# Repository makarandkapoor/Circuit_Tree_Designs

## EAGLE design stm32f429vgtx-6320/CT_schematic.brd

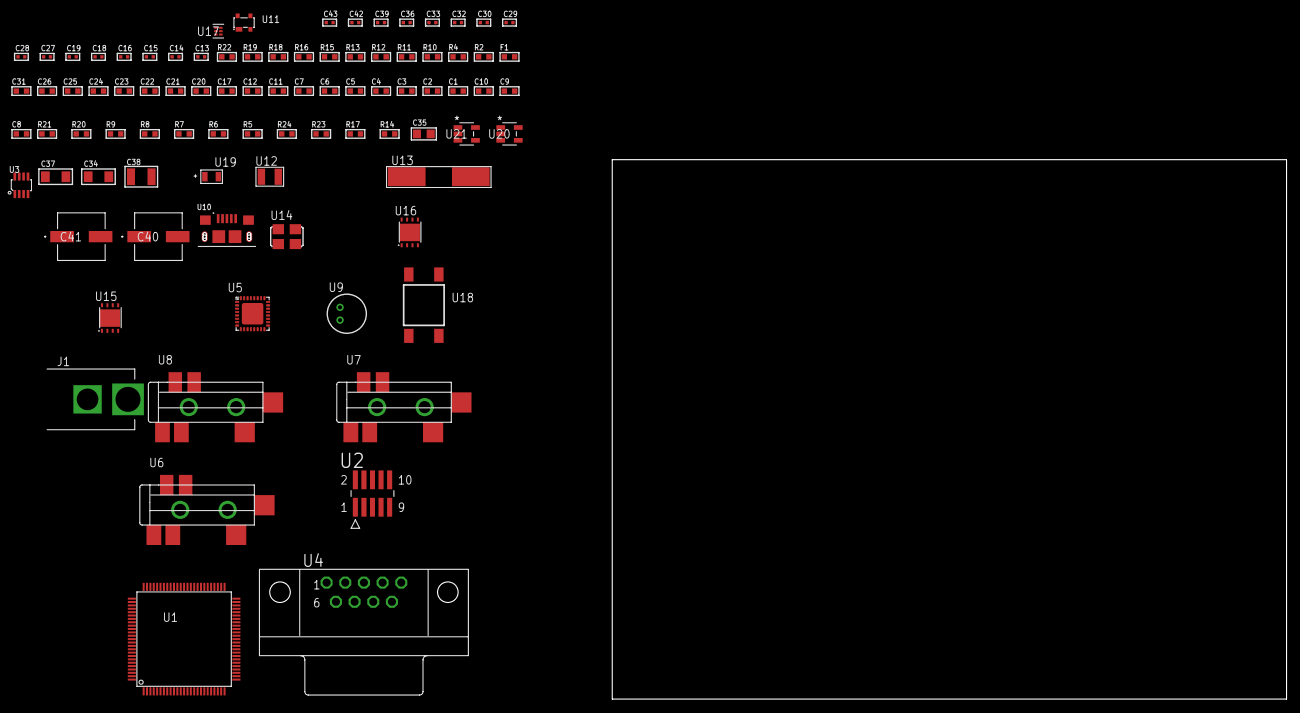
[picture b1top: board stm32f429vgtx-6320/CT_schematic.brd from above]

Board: 2 copper layers, 88 parts (0 on the bottom side), 56 nets, no tracks yet.

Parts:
C1, C12, C17, C20, C21, C22, C23, C24, C25, C26, C31: 1e-06; C0603
C2, C3, C4, C5, C6, C7: 1e-07; C0603
C8: 4.7e-06; C0603
C9, C10: 2.2e-09; C0603
C11: 1e-08; C0603
C13, C14, C15, C16: 1e-11; C0402
C18, C19, C27, C28, C29, C30, C39: 1e-07; C0402
C32, C33, C36, C42, C43: 1e-08; C0402
C34, C37: 1e-05; C1206
C35: 1e-05; C0805
C38: 1e-05; C1210
C40, C41: 0.0001; EXV-9H
F1: 240.0; L0603
J1: PJ-037B; PJ-037B_PACKAGE
R2, R16, R19: 1000.0; R0603
R4: 4700.0; R0603
R5, R6, R7, R8, R9, R20, R21: 10000.0; R0603
R10: 5.0; R0603
R11: 120.0; R0603
R12, R13: 1270.0; R0603
R14, R17: 100000.0; R0603
R15: 200.0; R0603
R18: 2231.0; R0603
R22: 9100.0; R0603
R23: 680000.0; R0603
R24: 120000.0; R0603
U1: STM32F429VGT6; LQFP100
U2: FTSH-105-01-L-DV-K; SAMTEC_FTSH-105-01-L-DV-K
U3: MAX3051EKA+T; SOT-23-8
U4: 182-009-113R531; 182-009-MALE
U5: SGTL5000XNAA3; QFN-32
U6, U7, U8: SJ-43515TS-SMT-TR
U9: WM-64PCT; WM-64PC
U10: 10118193-0001LF; FCI_10118193-0001LF
U11: prtr5v0u2ax; SOT143B
U12: ABS07-32.768KHZ-7-T
U13: ABLS-25.000MHZ-B2F-T
U14: ASFL-24.57MHZ-NCS; ASFL1
U15, U16: LP3878SDX-ADJ/NOPB; WSON-8
U17: TPS3895ADRYR; SON-6
U18: 4-1437565-2; SW_4-1437565-2
U19: Q65110A2395; LGM67K-G1J2-24-Z
U20, U21: nc7sz125m5x; NC7SZ125M5X

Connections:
CLK_CRYSTAL_U1_8: C13.1, U1.8, U12.1
CLK_CRYSTAL_U1_9: C14.1, U1.9, U12.2
CLK_CRYSTAL_U1_12: C15.1, U1.12, U13.1
CLK_CRYSTAL_U1_13: C16.1, U1.13, U13.2
CLK_U5_21: U5.21, U14.3
GND: C1.2, C2.2, C3.2, C4.2, C5.2, C6.2, C7.2, C8.2, C9.2, C10.2, C11.2, C12.2, C13.2, C14.2, C15.2, C16.2, C17.2, C18.2, C19.2, C27.2, C28.2, C29.2, C30.2, C31.2, C32.2, C33.2, C34.2, C35.2, C36.2, C37.2, C38.2, C39.2, C40.2, C41.2, C42.2, C43.2, J1.2, R2.2, R6.2, R10.2, R13.2, R16.2, R19.2, R22.2, R24.2, U1.10, U1.20, U1.27, U1.70, U1.74, U1.99, U2.3, U2.5, U3.2, U3.8, U4.5, U5.1, U5.3, U5.7, U5.EXP, U7.1, U8.1, U9.2, U10.5, U10.6, U10.7, U10.8, U10.9, U11.1, U14.2, U15.3, U15.PAD, U16.3, U16.PAD, U17.2, U19.C, U20.2, U20.3, U21.1, U21.3
NET_U1_14: R4.1, U1.14, U21.4
NET_U1_22: C11.1, C12.1, F1.1, U1.21, U1.22
NET_U1_37: R6.1, U1.37
NET_U1_49: C9.1, U1.49
NET_U1_73: C10.1, U1.73
NET_U1_94: R5.1, U1.94
NET_U1_98: U18.3, U18.4
NET_U2_9: R10.1, U2.9
NET_U3_6: R11.2, U3.6
NET_U4_2: R11.2, U3.6, U4.2
NET_U4_3: R11.1, U3.7, U4.3
NET_U5_10: C30.1, U5.10
NET_U5_29: R12.1, U5.29
NET_U5_31: R13.1, U5.31
NET_U6_1: U5.4, U6.1
NET_U6_2: U5.2, U6.2
NET_U6_5: U5.6, U6.5
NET_U7_2: C21.1, U7.2
NET_U7_5: C20.1, U7.5
NET_U8_2: C23.1, C24.1, U8.2
NET_U8_5: C22.1, U8.5
NET_U8_13: C23.2, C24.2
NET_U9_1: C25.1, C26.1, C31.1, U5.16, U9.1
NET_U9_15: C25.2, C26.2
NET_U15_1: C33.1, U15.1
NET_U15_6: R15.2, R16.1, U15.6
NET_U15_8: R14.1, U15.8
NET_U16_1: C36.1, U16.1
NET_U16_6: R18.2, R19.1, U16.6
NET_U16_8: R17.1, U16.8
NET_U17_1: R21.1, R22.1, U17.1
NET_U17_3: R23.2, R24.1, U17.3
NET_U17_4: R20.1, U17.4, U20.4, U21.2
NET_U18_1: R2.1, U18.1, U18.2
PROC_CAN1_RX: U1.81, U3.4
PROC_CAN1_TX: U1.82, U3.1
PROC_I2S2_CK: U1.47, U5.24
PROC_I2S2_EXT_SD: U1.17, U5.25
PROC_I2S2_SD: U1.18, U5.26
PROC_I2S2_WS: U1.51, U5.23
PROC_SYS_JTCK_SWCLK: R8.1, U1.76, U2.4
PROC_SYS_JTDO_SWO: U1.89, U2.6
PROC_SYS_JTMS_SWDIO: R9.1, U1.72, U2.2
PROC_USB_OTG_FS_DM: U1.70, U10.2, U11.3
PROC_USB_OTG_FS_DP: U1.71, U10.3, U11.2
PROC_USB_OTG_FS_VBUS: C17.1, U1.68, U10.1, U11.4
RST_OUT_U2_JTAG_RST_B: R7.1, U2.10, U20.1
VCC_S1_5V6: C34.1, C37.1, C40.1, C41.1, J1.1, R14.2, R17.2, U15.4, U16.4
VCC_TIER1_1V2: C27.1, C35.1, R15.1, U5.30, U15.5
VCC_TIER1_3V3: C1.1, C2.1, C3.1, C4.1, C5.1, C6.1, C7.1, C8.1, C18.1, C19.1, C28.1, C29.1, C32.1, C38.1, C39.1, C42.1, C43.1, F1.2, R4.2, R5.2, R7.2, R8.2, R9.2, R12.2, R18.1, R20.2, R21.2, R23.1, U1.6, U1.11, U1.19, U1.28, U1.50, U1.75, U1.100, U2.1, U3.3, U5.5, U5.20, U14.4, U16.5, U17.6, U20.5, U21.5

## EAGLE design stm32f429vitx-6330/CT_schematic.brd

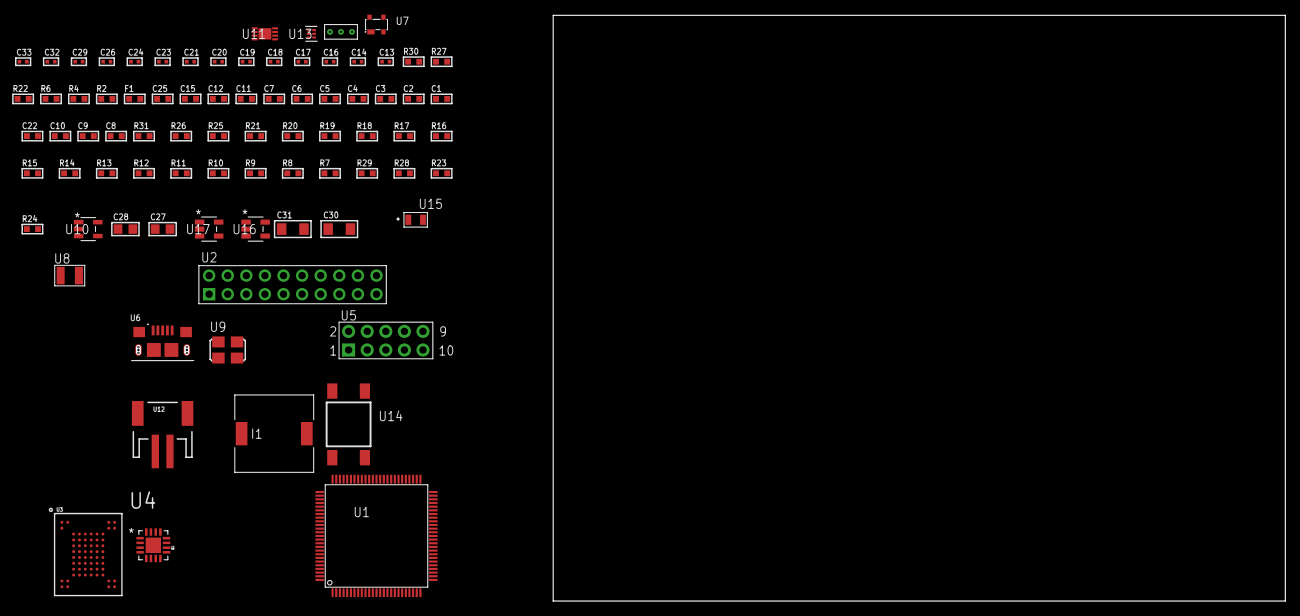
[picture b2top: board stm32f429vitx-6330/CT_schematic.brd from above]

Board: 2 copper layers, 81 parts (0 on the bottom side), 56 nets, no tracks yet.

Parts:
C1, C12, C15, C25: 1e-06; C0603
C2, C3, C4, C5, C6, C7: 1e-07; C0603
C8: 4.7e-06; C0603
C9, C10: 2.2e-09; C0603
C11: 1e-08; C0603
C13, C14: 1e-11; C0402
C16, C17, C18, C19, C20, C21, C23, C24, C29: 1e-07; C0402
C22: 2.2e-06; C0603
C26, C32, C33: 1e-08; C0402
C27, C28: 1e-05; C0805
C30, C31: 1e-05; C1206
F1: 240.0; L0603
I1: 2.5e-06; DR1040
R2: 1000.0; R0603
R4: 4700.0; R0603
R6: 2200.0; R0603
R7, R8, R9, R10, R11, R12, R13, R14, R15, R16, R17, R18, R19, R20, R21, R25, R26, R31: 10000.0; R0603
R22: 47.0; R0603
R23: 220000.0; R0603
R24: 1000000.0; R0603
R27: 9100.0; R0603
R28: 680000.0; R0603
R29: 120000.0; R0603
R30: 2000.0; R0603
U1: STM32F429VIT6; LQFP100
U2: TST-110-05-T-D-RA
U3: mt29f4g08abadah4; VFBGA-63
U4: TSC2013QRSARQ1; QFN65P400X400X100-17N
U5: HTSS-105-01-G-D
U6: 10118193-0001LF; FCI_10118193-0001LF
U7: prtr5v0u2ax; SOT143B
U8: ABS07-32.768KHZ-7-T
U9: ASFL1-25MHZ-NCS; ASFL1
U10: ltc3406es5; TSOT-23-5
U11: MCP73831T-2ACI/MC; DFN8_2X3MC
U12: S2B-PH-SM4-TB(LF)(SN); JST-2-SMD
U13: TPS3895ADRYR; SON-6
U14: 4-1437565-2; SW_4-1437565-2
U15: Q65110A2395; LGM67K-G1J2-24-Z
U16, U17: nc7sz125m5x; NC7SZ125M5X
U18: Dummy; DUMMY_PACKAGE_174

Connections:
CLK_CRYSTAL_U1_8: C13.1, U1.8, U8.1
CLK_CRYSTAL_U1_9: C14.1, U1.9, U8.2
CLK_U1_12: U1.12, U9.3
GND: C1.2, C2.2, C3.2, C4.2, C5.2, C6.2, C7.2, C8.2, C9.2, C10.2, C11.2, C12.2, C13.2, C14.2, C15.2, C16.2, C17.2, C18.2, C19.2, C20.2, C21.2, C22.2, C26.2, C27.2, C28.1, C28.2, C29.2, C30.2, C31.2, C32.2, C33.2, R2.2, R8.2, R14.2, R23.2, R27.2, R29.2, R30.2, U1.10, U1.20, U1.27, U1.70, U1.74, U1.99, U2.4, U2.6, U2.8, U2.10, U2.12, U2.14, U2.16, U2.18, U2.20, U3.C5, U3.F7, U3.K3, U3.K8, U4.17, U5.9, U6.5, U6.6, U6.7, U6.8, U6.9, U7.1, U9.2, U10.2, U11.6, U11.9, U12.2, U13.2, U15.C, U16.2, U16.3, U17.1, U17.3, U18.1
INPUT_USBPOWER_5V: C15.1, C30.1, R31.2, U1.68, U6.1, U7.4, U11.1, U11.2
NET_U1_14: R4.1, U1.14, U17.4
NET_U1_22: C11.1, C12.1, F1.1, U1.21, U1.22
NET_U1_37: R8.1, U1.37
NET_U1_49: C9.1, U1.49
NET_U1_73: C10.1, U1.73
NET_U1_93: R6.1, U1.93, U4.1
NET_U1_94: R7.1, U1.94
NET_U1_98: U14.3, U14.4
NET_U2_19: R14.1, U2.19
NET_U3_C3: R19.1, U3.C3
NET_U3_C8: R15.1, U3.C8
NET_U4_4: R21.1, U4.4
NET_U4_5: R20.1, U4.5
NET_U4_9: C23.2, C24.2, C25.2, R22.2, U4.9
NET_U4_15: R22.1, U4.8, U4.15
NET_U5_3: U4.12, U5.3
NET_U5_4: U4.14, U5.4
NET_U5_5: U4.11, U5.5
NET_U5_6: U4.13, U5.6
NET_U10_3: I1.1, U10.3
NET_U10_5: R23.1, R24.1, U10.5
NET_U10_ATNET_3: I1.2, R24.2
NET_U11_5: R31.1, U11.5
NET_U11_8: R30.1, U11.8
NET_U13_1: R26.1, R27.1, U13.1
NET_U13_3: R28.2, R29.1, U13.3
NET_U13_4: R25.1, U13.4, U16.4, U17.2
NET_U14_1: R2.1, U14.1, U14.2
PROC_FMC_D0: U1.61, U3.H4
PROC_FMC_D1: U1.62, U3.J4
PROC_FMC_D2: U1.81, U3.K4
PROC_FMC_D3: U1.82, U3.K5
PROC_FMC_D4: U1.38, U3.K6
PROC_FMC_D5: U1.39, U3.J7
PROC_FMC_D6: U1.40, U3.K7
PROC_FMC_D7: U1.41, U3.J8
PROC_FMC_NCE2: R16.1, U1.88, U3.C6
PROC_FMC_NOE: R18.1, U1.85, U3.D4
PROC_FMC_NWE: R17.1, U1.86, U3.C7
PROC_SYS_JTCK_SWCLK: R12.1, U1.76, U2.9
PROC_SYS_JTDI: R10.1, U1.77, U2.5
PROC_SYS_JTDO_SWO: U1.89, U2.13
PROC_SYS_JTMS_SWDIO: R11.1, U1.72, U2.7
PROC_SYS_JTRST: R9.1, U1.90, U2.3
PROC_TIM1_CH2: U1.42, U18.2
PROC_TIM1_CH4: U1.45, U18.3
PROC_USB_OTG_FS_DM: U1.70, U6.2, U7.3
PROC_USB_OTG_FS_DP: U1.71, U6.3, U7.2
RST_OUT_U2_SRESET_B: R13.1, U2.15, U16.1
VCC_S1_3V7: C27.1, C31.1, U10.4, U11.3, U11.4, U12.1
VCC_TIER1_3V3: C1.1, C2.1, C3.1, C4.1, C5.1, C6.1, C7.1, C8.1, C16.1, C17.1, C18.1, C19.1, C20.1, C21.1, C22.1, C23.1, C24.1, C25.1, C26.1, C28.2, C29.1, C32.1, C33.1, F1.2, I1.2, R4.2, R6.2, R7.2, R9.2, R10.2, R11.2, R12.2, R13.2, R15.2, R16.2, R17.2, R18.2, R19.2, R20.2, R21.2, R24.2, R25.2, R26.2, R28.1, U1.6, U1.11, U1.19, U1.28, U1.50, U1.75, U1.100, U2.1, U2.2, U3.D3, U3.G4, U3.H8, U3.J6, U4.7, U4.10, U9.4, U13.6, U16.5, U17.5

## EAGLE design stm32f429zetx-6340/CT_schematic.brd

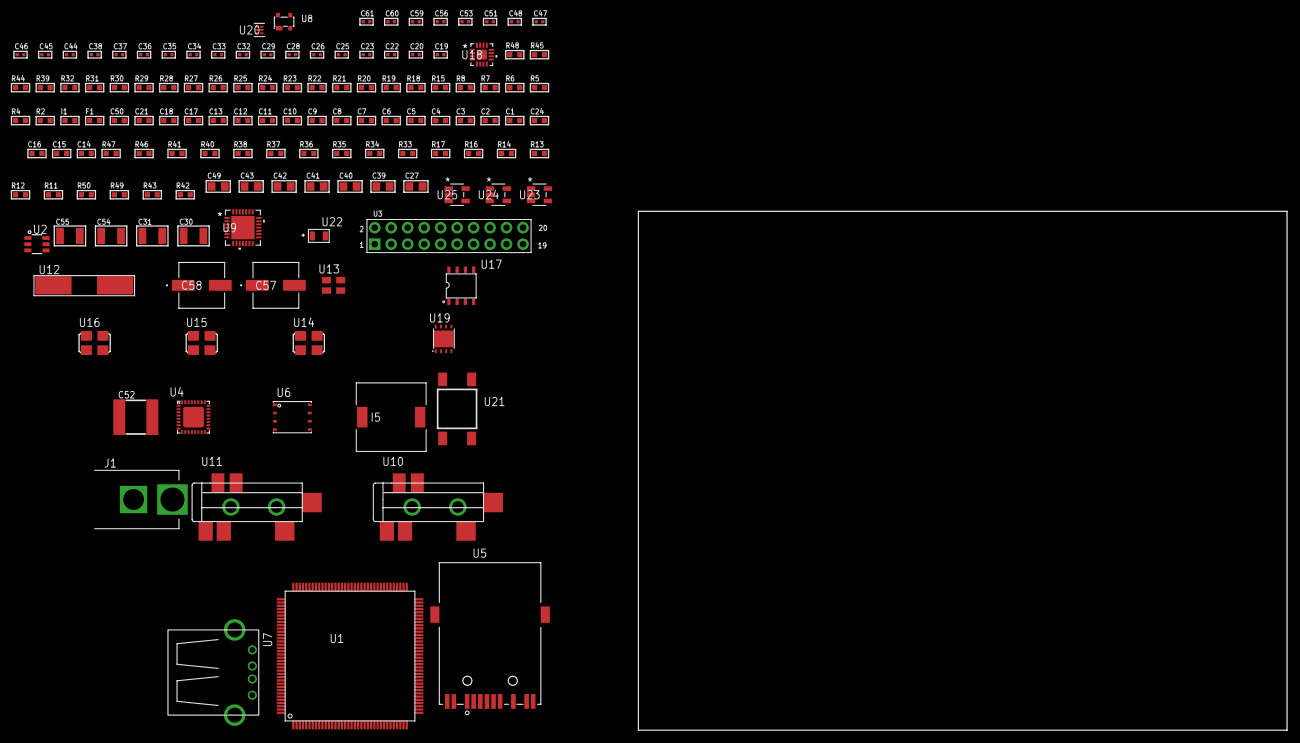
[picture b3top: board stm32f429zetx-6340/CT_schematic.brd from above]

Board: 2 copper layers, 100.0 x 80.0 mm, 136 parts (0 on the bottom side), 91 nets, no tracks yet.

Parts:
C1, C18, C21, C50: 1e-06; C0603
C2, C3, C4, C5, C6, C7, C8, C9, C10, C11, C12, C13: 1e-07; C0603
C14: 4.7e-06; C0603
C15, C16: 2.2e-09; C0603
C17: 1e-08; C0603
C19, C20: 1e-11; C0402
C22, C23, C25, C26, C28, C34, C35, C36, C37, C38, C51, C56: 1e-07; C0402
C24: 2.2e-06; C0603
C27, C39, C40, C41, C42, C43, C49: 1e-05; C0805
C29, C44, C45, C46, C47, C48, C53, C59, C60, C61: 1e-08; C0402
C30, C31: 2.2e-05; C1210
C32, C33: 1e-09; C0402
C52: 6.8e-05; 2220
C54, C55: 1e-05; C1210
C57, C58: 0.0001; EXV-9H
F1: 240.0; L0603
I1: 97.0; R0603
I5: 7e-06; DR1040
J1: PJ-037B; PJ-037B_PACKAGE
R2, R27, R29, R30, R45: 1000.0; R0603
R4, R5, R6, R23, R24, R25, R26, R28, R31, R32: 4700.0; R0603
R7, R8: 2200.0; R0603
R11, R36, R37, R38: 47000.0; R0603
R12, R13, R14, R16, R17, R33, R34, R35, R46, R47: 10000.0; R0603
R15: 1270.0; R0603
R18, R19: 0.1; R0603
R20: 200.0; R0603
R21: 220.0; R0603
R22: 6490.0; R0603
R39: 680.0; R0603
R40: 20000.0; R0603
R41: 91000.0; R0603
R42: 300000.0; R0603
R43: 100000.0; R0603
R44: 3900.0; R0603
R48: 9100.0; R0603
R49: 680000.0; R0603
R50: 120000.0; R0603
U1: STM32F429ZET6; LQFP144
U2: MAX4995AAUT+T; SOT-23-6
U3: arducam_ov2640; ARDUCAM
U4: KSZ8081RNBIA-TR; QFN-32
U5: 7498011122R
U6: 24AA256-I/MF; DFN8-S
U7: 61400416021; USB-A-H
U8: prtr5v0u2ax; SOT143B
U9: WM8731CLSEFL; QFN-28
U10, U11: SJ-43515TS-SMT-TR
U12: ABLS-25.000MHZ-B2F-T
U13: ASEK-32.768KHz-ECST; ASEK
U14: ASFL1-12.288MHZ-EC-T; ASFL1
U15: ASFL1-25MHZ-NCS; ASFL1
U16: ASFL1-50MHZ-NCS; ASFL1
U17: idt74fct38072; IDT74FCT38072
U18: LTC3601EUD#PBF; QFN-16_EP
U19: LP3878SDX-ADJ/NOPB; WSON-8
U20: TPS3895ADRYR; SON-6
U21: 4-1437565-2; SW_4-1437565-2
U22: Q65110A2395; LGM67K-G1J2-24-Z
U23, U24, U25: nc7sz125m5x; NC7SZ125M5X

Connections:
CLK_CRYSTAL_U1_23: C19.1, U1.23, U12.1
CLK_CRYSTAL_U1_24: C20.1, U1.24, U12.2
CLK_U1_8: U1.8, U13.3
CLK_U1_35: U1.35, U17.7
CLK_U3_8: U3.8, U15.3
CLK_U4_9: U4.9, U17.6
CLK_U9_1: U9.1, U14.3
CLK_U17_3: U16.3, U17.3
GND: C1.2, C2.2, C3.2, C4.2, C5.2, C6.2, C7.2, C8.2, C9.2, C10.2, C11.2, C12.2, C13.2, C14.2, C15.2, C16.2, C17.2, C18.2, C19.2, C20.2, C21.2, C22.2, C23.2, C24.2, C25.2, C26.2, C27.2, C28.2, C29.2, C33.2, C34.2, C35.2, C36.2, C37.2, C38.2, C39.2, C40.2, C41.2, C42.2, C43.2, C44.2, C45.2, C46.2, C47.2, C48.2, C49.2, C50.2, C52.1, C52.2, C53.2, C54.2, C55.2, C56.2, C57.2, C58.2, C59.2, C60.2, C61.2, J1.2, R2.2, R11.2, R14.2, R15.2, R17.2, R18.2, R19.2, R22.2, R24.2, R27.2, R29.2, R30.2, R33.2, R36.2, R37.2, R38.2, R40.2, R42.2, R45.2, R48.2, R50.2, U1.16, U1.31, U1.38, U1.51, U1.61, U1.83, U1.94, U1.107, U1.120, U1.130, U2.2, U3.2, U3.20, U4.1, U4.EXP, U5.1, U5.10, U6.4, U7.4, U7.5, U7.6, U8.1, U9.4, U9.15, U9.19, U9.25, U9.26, U9.29, U10.1, U11.1, U13.2, U14.2, U15.2, U16.2, U17.4, U17.5, U17.8, U18.1, U18.9, U18.17, U19.3, U19.PAD, U20.2, U22.C, U23.1, U23.3, U24.1, U24.3, U25.1, U25.3
NET_U1_25: R5.1, U1.25, U24.4
NET_U1_33: C17.1, C18.1, F1.1, U1.32, U1.33
NET_U1_48: R14.1, U1.48
NET_U1_71: C15.1, U1.71
NET_U1_102: R15.1, U1.102
NET_U1_106: C16.1, U1.106
NET_U1_136: R7.1, U1.136, U6.6
NET_U1_137: R8.1, U1.137, U6.5
NET_U1_138: R13.1, U1.138
NET_U1_142: U21.3, U21.4
NET_U1_143: R12.1, U1.143
NET_U2_3: R11.1, U2.3
NET_U3_19: R6.1, U3.19, U25.4
NET_U4_2: C24.1, C25.1, U4.2
NET_U4_3: C26.1, I1.1, U4.3
NET_U4_10: R22.1, U4.10
NET_U4_13: R25.1, U4.13
NET_U4_14: R26.1, U4.14
NET_U4_19: R24.1, U4.19
NET_U4_20: R30.1, U4.20
NET_U4_21: R23.1, U4.21
NET_U4_28: R28.1, U4.28
NET_U4_29: R29.1, U4.29
NET_U4_31: R31.1, U4.31
NET_U4_32: R4.1, U4.32, U23.4
NET_U5_1: U4.7, U5.1
NET_U5_2: C22.1, U5.2
NET_U5_3: U4.6, U5.3
NET_U5_4: U4.5, U5.4
NET_U5_5: C23.1, U5.5
NET_U5_6: U4.4, U5.6
NET_U5_8: R19.1, U5.8
NET_U5_9: R20.1, U5.9
NET_U5_12: R21.1, U5.12
NET_U5_13: R18.1, U5.13, U5.14
NET_U6_1: R33.1, U6.1
NET_U6_2: R34.1, U6.2
NET_U6_3: R35.1, U6.3
NET_U9_20: C38.1, C43.1, U9.20
NET_U10_2: C31.1, R37.1, U10.2
NET_U10_5: C30.1, R36.1, U10.5
NET_U11_5: C32.1, C33.1, R38.1, R39.1, U11.5
NET_U18_3: C51.2, I5.1, U18.3, U18.4
NET_U18_6: C51.1, U18.6
NET_U18_7: C50.1, U18.7, U18.12
NET_U18_10: R42.1, U18.10
NET_U18_11: R40.1, R41.1, U18.11
NET_U18_ATNET_3: I5.2, R41.2
NET_U19_1: C53.1, U19.1
NET_U19_6: R44.2, R45.1, U19.6
NET_U19_8: R43.1, U19.8
NET_U20_1: R47.1, R48.1, U20.1
NET_U20_3: R49.2, R50.1, U20.3
NET_U20_4: R46.1, U20.4, U23.2, U24.2, U25.2
NET_U21_1: R2.1, U21.1, U21.2
PROC_DCMI_D0: U1.96, U3.18
PROC_DCMI_D1: U1.97, U3.17
PROC_DCMI_D2: U1.98, U3.16
PROC_DCMI_D3: U1.99, U3.15
PROC_DCMI_D4: U1.3, U3.14
PROC_DCMI_D5: U1.117, U3.13
PROC_DCMI_D6: U1.4, U3.12
PROC_DCMI_D7: U1.5, U3.11
PROC_DCMI_D8: U1.111, U3.10
PROC_DCMI_D9: U1.113, U3.9
PROC_DCMI_HSYNC: U1.40, U3.6
PROC_DCMI_PIXCK: U1.42, U3.7
PROC_DCMI_VSYNC: U1.124, U3.5
PROC_ETH_RXD0: R32.1, U4.16
PROC_ETH_RXD1: R27.1, U4.15
PROC_GPIO_TO_U1_USB_FAULT: R16.1, U1.2, U2.6
PROC_GPIO_TO_U1_VBUS_EN: R17.1, U1.1, U2.4
PROC_I2S2_CK: U1.69, U9.7
PROC_I2S2_EXT_SD: U1.28, U9.10
PROC_I2S2_SD: U1.29, U9.8
PROC_I2S2_WS: U1.140, U9.9, U9.11
PROC_USB_OTG_FS_DM: U1.103, U7.2, U8.3
PROC_USB_OTG_FS_DP: U1.104, U7.3, U8.2
PROC_USB_OTG_FS_VBUS: U1.101, U2.1, U7.1, U8.4
VCC_S1_14V9: C49.1, C54.1, C57.1, C58.1, J1.1, R43.2, U18.15, U18.16, U19.4
VCC_TIER1_3V3: C1.1, C2.1, C3.1, C4.1, C5.1, C6.1, C7.1, C8.1, C9.1, C10.1, C11.1, C12.1, C13.1, C14.1, C21.1, C27.1, C28.1, C29.1, C34.1, C35.1, C36.1, C37.1, C39.1, C40.1, C41.1, C42.1, C44.1, C45.1, C46.1, C47.1, C48.1, C52.2, C56.1, C59.1, C60.1, C61.1, F1.2, I1.2, I5.2, R4.2, R5.2, R6.2, R7.2, R8.2, R12.2, R13.2, R16.2, R23.2, R25.2, R26.2, R28.2, R31.2, R32.2, R34.2, R35.2, R41.2, R46.2, R47.2, R49.1, U1.6, U1.17, U1.30, U1.39, U1.52, U1.62, U1.72, U1.84, U1.95, U1.108, U1.121, U1.131, U1.144, U3.1, U4.17, U6.7, U6.8, U9.3, U9.5, U9.12, U9.18, U13.4, U14.4, U15.4, U16.4, U17.1, U17.2, U18.8, U20.6, U23.5, U24.5, U25.5
VCC_TIER1_5V0: C55.1, R44.1, U2.5, U19.5

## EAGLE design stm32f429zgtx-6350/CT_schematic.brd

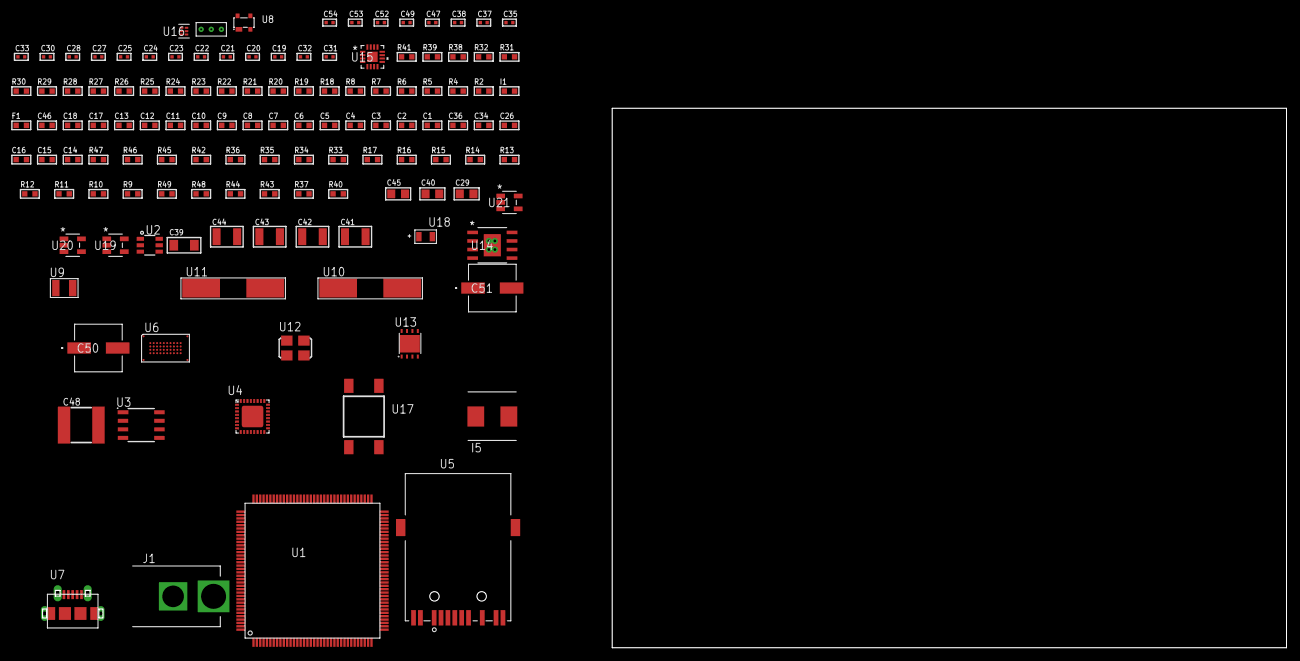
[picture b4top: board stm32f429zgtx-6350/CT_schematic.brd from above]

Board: 2 copper layers, 127 parts (0 on the bottom side), 110 nets, no tracks yet.

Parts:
C1, C18, C46: 1e-06; C0603
C2, C3, C4, C5, C6, C7, C8, C9, C10, C11, C12, C13: 1e-07; C0603
C14: 4.7e-06; C0603
C15, C16: 2.2e-09; C0603
C17: 1e-08; C0603
C19, C20, C21, C22: 1e-11; C0402
C23, C37, C38, C52, C53, C54: 1e-08; C0402
C24, C25, C27, C28, C30, C33, C35, C47, C49: 1e-07; C0402
C26, C34, C36: 2.2e-06; C0603
C29, C40, C45: 1e-05; C0805
C31, C32: 2.2e-11; C0402
C39: 1e-05; C1206
C41, C42, C43, C44: 1e-05; C1210
C48: 6.8e-05; 2220
C50, C51: 0.0001; EXV-9H
F1: 240.0; L0603
I1: 97.0; R0603
I5: 3.3e-06; WE-HCI_7030/7040/7050
J1: PJ-037B; PJ-037B_PACKAGE
R2, R25, R27, R29, R32, R39: 1000.0; R0603
R4, R5, R6, R23, R24, R26, R28, R30, R31: 4700.0; R0603
R7, R8, R41: 2200.0; R0603
R9: 47000.0; R0603
R10, R11, R12, R13, R14, R15, R16, R17, R33, R34, R35, R36, R45, R46: 10000.0; R0603
R18, R19: 0.1; R0603
R20: 200.0; R0603
R21: 220.0; R0603
R22: 6490.0; R0603
R37: 100000.0; R0603
R38: 806.0; R0603
R40: 4031.5447154472; R0603
R42: 20000.0; R0603
R43: 150000.0; R0603
R44, R48: 300000.0; R0603
R47: 82000.0; R0603
R49: 120000.0; R0603
U1: STM32F429ZGT6; LQFP144
U2: MAX4995AAUT+T; SOT-23-6
U3: AT25M02-SSHD-T; SOIC-8
U4: KSZ8081RNBIA-TR; QFN-32
U5: 7498011122R
U6: S29VS256RABBHW000
U7: 47590-0001; MICRO_USB_AB
U8: prtr5v0u2ax; SOT143B
U9: ABS07-32.768KHZ-7-T
U10, U11: ABLS-25.000MHZ-B2F-T
U12: ASFL1-50MHZ-NCS; ASFL1
U13: LP3878SDX-ADJ/NOPB; WSON-8
U14: MIC5234YME; SOIC-8_EP
U15: LTC3601EUD#PBF; QFN-16_EP
U16: TPS3895ADRYR; SON-6
U17: 4-1437565-2; SW_4-1437565-2
U18: Q65110A2395; LGM67K-G1J2-24-Z
U19, U20, U21: nc7sz125m5x; NC7SZ125M5X
U22: Dummy; DUMMY_PACKAGE_256

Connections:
CLK_CRYSTAL_U1_8: C19.1, U1.8, U9.1
CLK_CRYSTAL_U1_9: C20.1, U1.9, U9.2
CLK_CRYSTAL_U1_23: C21.1, U1.23, U10.1
CLK_CRYSTAL_U1_24: C22.1, U1.24, U10.2
CLK_CRYSTAL_U4_8: C31.1, U4.8, U11.2
CLK_CRYSTAL_U4_9: C32.1, U4.9, U11.1
CLK_U1_35: U1.35, U12.3
GND: C1.2, C2.2, C3.2, C4.2, C5.2, C6.2, C7.2, C8.2, C9.2, C10.2, C11.2, C12.2, C13.2, C14.2, C15.2, C16.2, C17.2, C18.2, C19.2, C20.2, C21.2, C22.2, C23.2, C24.2, C25.2, C26.2, C27.2, C28.2, C29.2, C30.2, C31.2, C32.2, C33.2, C34.2, C35.2, C36.2, C37.2, C38.2, C39.2, C40.2, C41.2, C42.2, C43.2, C44.2, C45.2, C46.2, C48.1, C48.2, C49.2, C50.2, C51.2, C52.2, C53.2, C54.2, J1.2, R2.2, R9.2, R12.2, R14.2, R18.2, R19.2, R22.2, R24.2, R25.2, R27.2, R29.2, R32.2, R39.2, R41.2, R42.2, R44.2, R47.2, R49.2, U1.16, U1.31, U1.38, U1.51, U1.61, U1.83, U1.94, U1.107, U1.120, U1.130, U2.2, U3.4, U4.1, U4.EXP, U5.1, U5.10, U6.C5, U6.D12, U6.E3, U6.F5, U7.5, U7.6, U7.7, U7.8, U7.9, U8.1, U12.2, U13.3, U13.PAD, U14.7, U14.EPAD, U15.1, U15.9, U15.17, U16.2, U18.C, U19.1, U19.3, U20.1, U20.3, U21.1, U21.3, U22.1
NET_U1_25: R6.1, U1.25, U21.4
NET_U1_27: R7.1, U1.27, U4.12
NET_U1_33: C17.1, C18.1, F1.1, U1.32, U1.33
NET_U1_36: R8.1, U1.36, U4.11
NET_U1_48: R12.1, U1.48
NET_U1_71: C15.1, U1.71
NET_U1_106: C16.1, U1.106
NET_U1_138: R11.1, U1.138
NET_U1_142: U17.3, U17.4
NET_U1_143: R10.1, U1.143
NET_U2_3: R9.1, U2.3
NET_U3_3: R15.1, U3.3
NET_U3_7: R17.1, U3.7
NET_U4_2: C26.1, C27.1, U4.2
NET_U4_3: C28.1, I1.1, U4.3
NET_U4_10: R22.1, U4.10
NET_U4_13: R25.1, U4.13
NET_U4_14: R26.1, U4.14
NET_U4_19: R24.1, U4.19
NET_U4_20: R30.1, U4.20
NET_U4_21: R23.1, U4.21
NET_U4_28: R28.1, U4.28
NET_U4_29: R29.1, U4.29
NET_U4_31: R31.1, U4.31
NET_U4_32: R4.1, U4.32, U19.4
NET_U5_1: U4.7, U5.1
NET_U5_2: C24.1, U5.2
NET_U5_3: U4.6, U5.3
NET_U5_4: U4.5, U5.4
NET_U5_5: C25.1, U5.5
NET_U5_6: U4.4, U5.6
NET_U5_8: R19.1, U5.8
NET_U5_9: R20.1, U5.9
NET_U5_12: R21.1, U5.12
NET_U5_13: R18.1, U5.13, U5.14
NET_U6_D8: R5.1, U6.D8, U20.4
NET_U13_1: C38.1, U13.1
NET_U13_6: R38.2, R39.1, U13.6
NET_U13_8: R37.1, U13.8
NET_U14_4: R40.2, R41.1, U14.4
NET_U15_3: C47.2, I5.1, U15.3, U15.4
NET_U15_6: C47.1, U15.6
NET_U15_7: C46.1, U15.7, U15.12
NET_U15_10: R44.1, U15.10
NET_U15_11: R42.1, R43.1, U15.11
NET_U15_ATNET_3: I5.2, R43.2
NET_U16_1: R46.1, R47.1, U16.1
NET_U16_3: R48.2, R49.1, U16.3
NET_U16_4: R45.1, U16.4, U19.2, U20.2, U21.2
NET_U17_1: R2.1, U17.1, U17.2
PROC_ADC1_IN3: U1.37, U22.2
PROC_ADC1_IN12: U1.28, U22.3
PROC_ETH_CRS_DV: U1.43, U4.18
PROC_ETH_RXD0: R32.1, U1.44, U4.16
PROC_ETH_RXD1: R27.1, U1.45, U4.15
PROC_ETH_TXD0: U1.73, U4.24
PROC_ETH_TXD1: U1.74, U4.25
PROC_ETH_TX_EN: U1.70, U4.23
PROC_FMC_A16: U1.80, U6.D4
PROC_FMC_A17: U1.81, U6.C11
PROC_FMC_A18: U1.82, U6.D10
PROC_FMC_A19: U1.2, U6.C10
PROC_FMC_A20: U1.3, U6.D5
PROC_FMC_A21: U1.4, U6.C4
PROC_FMC_A22: U1.5, U6.C12
PROC_FMC_A23: U1.1, U6.D7
PROC_FMC_CLK: U1.117, U6.C6
PROC_FMC_D0: U1.85, U6.F3
PROC_FMC_D1: U1.86, U6.F4
PROC_FMC_D2: U1.114, U6.E6
PROC_FMC_D3: U1.115, U6.E7
PROC_FMC_D4: U1.58, U6.F8
PROC_FMC_D5: U1.59, U6.F9
PROC_FMC_D6: U1.60, U6.E10
PROC_FMC_D7: U1.63, U6.E11
PROC_FMC_D8: U1.64, U6.E4
PROC_FMC_D9: U1.65, U6.E5
PROC_FMC_D10: U1.66, U6.F6
PROC_FMC_D11: U1.67, U6.F7
PROC_FMC_D12: U1.68, U6.E8
PROC_FMC_D13: U1.77, U6.E9
PROC_FMC_D14: U1.78, U6.F11
PROC_FMC_D15: U1.79, U6.F12
PROC_FMC_NE2: R34.1, U1.124, U6.D11
PROC_FMC_NL: U1.137, U6.D6
PROC_FMC_NOE: R36.1, U1.118, U6.E12
PROC_FMC_NWAIT: R33.1, U1.122, U6.C3
PROC_FMC_NWE: R35.1, U1.119, U6.C8
PROC_GPIO_TO_U1_USB_FAULT: R13.1, U1.10, U2.6
PROC_GPIO_TO_U1_VBUS_EN: R14.1, U1.7, U2.4
PROC_SPI1_MISO: U1.42, U3.2
PROC_SPI1_MOSI: U1.135, U3.5
PROC_SPI1_NSS: R16.1, U1.40, U3.1
PROC_SPI1_SCK: U1.41, U3.6
PROC_USB_OTG_FS_DM: U1.103, U7.2, U8.3
PROC_USB_OTG_FS_DP: U1.104, U7.3, U8.2
PROC_USB_OTG_FS_ID: U1.102, U7.4
PROC_USB_OTG_FS_VBUS: U1.101, U2.1, U7.1, U8.4
VCC_S1_5V9: C39.1, C41.1, C42.1, C45.1, C50.1, C51.1, J1.1, R37.2, U13.4, U14.5, U14.8, U15.15, U15.16
VCC_TIER1_1V8: C1.1, C2.1, C3.1, C4.1, C5.1, C6.1, C7.1, C8.1, C9.1, C10.1, C11.1, C12.1, C13.1, C14.1, C23.1, C29.1, C30.1, C33.1, C34.1, C35.1, C36.1, C40.1, C49.1, C52.1, C53.1, C54.1, F1.2, R4.2, R5.2, R6.2, R7.2, R8.2, R10.2, R11.2, R13.2, R15.2, R16.2, R17.2, R23.2, R26.2, R28.2, R30.2, R31.2, R33.2, R34.2, R35.2, R36.2, R38.1, R45.2, R46.2, R48.1, U1.6, U1.17, U1.30, U1.39, U1.52, U1.62, U1.72, U1.84, U1.95, U1.108, U1.121, U1.131, U1.144, U3.8, U4.17, U6.C7, U6.D3, U6.F10, U13.5, U16.6, U19.5, U20.5, U21.5
VCC_TIER1_3V3: C37.1, C43.1, C44.1, I1.2, R40.1, U12.4, U14.1
VCC_TIER1_5V0: C48.2, I5.2, R43.2, U2.5, U15.8

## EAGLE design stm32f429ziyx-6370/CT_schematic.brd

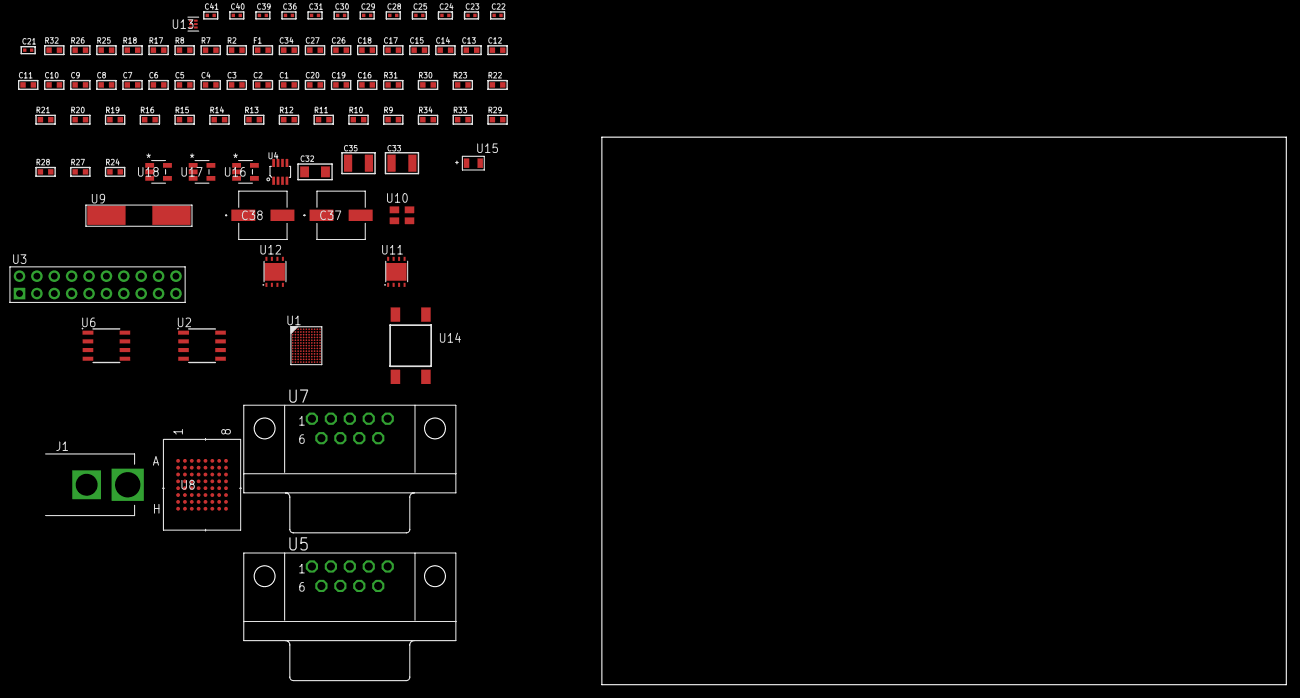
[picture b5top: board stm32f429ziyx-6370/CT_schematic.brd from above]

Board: 2 copper layers, 100.0 x 80.0 mm, 90 parts (0 on the bottom side), 92 nets, no tracks yet.

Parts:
C1, C18, C26, C27, C34: 1e-06; C0603
C2, C3, C4, C5, C6, C7, C8, C9, C10, C11, C12, C13, C14, C15: 1e-07; C0603
C16: 4.7e-06; C0603
C17: 1e-08; C0603
C19, C20: 2.2e-06; C0603
C21, C22: 1e-11; C0402
C23, C28, C29, C30, C31, C39, C40, C41: 1e-08; C0402
C24, C25, C36: 1e-07; C0402
C32: 1e-05; C1206
C33, C35: 1e-05; C1210
C37, C38: 0.0001; EXV-9H
F1: 240.0; L0603
J1: PJ-037B; PJ-037B_PACKAGE
R2, R26: 1000.0; R0603
R7, R8: 4700.0; R0603
R9, R10, R11, R12, R13, R14, R15, R16, R19, R20, R21, R22, R23, R30, R31: 10000.0; R0603
R17, R18: 120.0; R0603
R24, R27, R29: 100000.0; R0603
R25: 2231.0; R0603
R28: 300000.0; R0603
R32: 9100.0; R0603
R33: 680000.0; R0603
R34: 120000.0; R0603
U1: STM32F429ZIY6; WLCSP143
U2: AT25010B-SSHL-T; SOIC-8
U3: TST-110-05-T-D-RA
U4: MAX3051EKA+T; SOT-23-8
U5, U7: 182-009-113R531; 182-009-MALE
U6: MCP2562-E/SN; SOIC-8
U8: mt28ew256aba1HPC-0SIT; LBGA-64
U9: ABLS-25.000MHZ-B2F-T
U10: ASEK-32.768KHz-ECST; ASEK
U11: LP3878SDX-ADJ/NOPB; WSON-8
U12: LP2951ACSDX/NOPB; WSON-8
U13: TPS3895ADRYR; SON-6
U14: 4-1437565-2; SW_4-1437565-2
U15: Q65110A2395; LGM67K-G1J2-24-Z
U16, U17, U18: nc7sz125m5x; NC7SZ125M5X

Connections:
CLK_CRYSTAL_U1_H10: C21.1, U1.H10, U9.1
CLK_CRYSTAL_U1_J11: C22.1, U1.J11, U9.2
CLK_U1_D11: U1.D11, U10.3
GND: C1.2, C2.2, C3.2, C4.2, C5.2, C6.2, C7.2, C8.2, C9.2, C10.2, C11.2, C12.2, C13.2, C14.2, C15.2, C16.2, C17.2, C18.2, C19.2, C20.2, C21.2, C22.2, C23.2, C24.2, C25.2, C26.2, C27.2, C28.2, C29.2, C30.2, C31.2, C32.2, C33.2, C34.2, C35.2, C36.2, C37.2, C38.2, C39.2, C40.2, C41.2, J1.2, R2.2, R11.2, R12.2, R26.2, R29.2, R32.2, R34.2, U1.D2, U1.E7, U1.F5, U1.H2, U1.H3, U1.H7, U1.K10, U2.4, U3.4, U3.6, U3.8, U3.10, U3.12, U3.14, U3.16, U3.18, U3.20, U4.2, U4.8, U5.5, U6.2, U6.8, U7.5, U8.E8, U8.H2, U8.H7, U10.2, U11.3, U11.PAD, U12.3, U12.4, U12.PAD, U13.2, U15.C, U16.2, U16.3, U17.1, U17.3, U18.1, U18.3
NET_U1_A11: R9.1, U1.A11
NET_U1_C9: R10.1, U1.C9
NET_U1_D1: C20.1, U1.D1
NET_U1_H9: R8.1, U1.H9, U18.4
NET_U1_L7: R11.1, U1.L7
NET_U1_L10: C17.1, C18.1, F1.1, U1.L10, U1.L11
NET_U1_N2: C19.1, U1.N2
NET_U1_N10: U14.3, U14.4
NET_U1_N11: R12.1, U1.N11
NET_U2_3: R13.1, U2.3
NET_U2_7: R15.1, U2.7
NET_U4_6: R17.2, U4.6
NET_U5_2: R17.2, U4.6, U5.2
NET_U5_3: R17.1, U4.7, U5.3
NET_U6_6: R18.2, U6.6
NET_U7_2: R18.2, U6.6, U7.2
NET_U7_3: R18.1, U6.7, U7.3
NET_U8_B4: R22.1, U8.B4
NET_U8_B5: R7.1, U8.B5, U17.4
NET_U11_1: C31.1, U11.1
NET_U11_6: R25.2, R26.1, U11.6
NET_U11_8: R24.1, U11.8
NET_U12_5: R27.1, U12.5
NET_U12_7: R28.2, R29.1, U12.7
NET_U13_1: R31.1, R32.1, U13.1
NET_U13_3: R33.2, R34.1, U13.3
NET_U13_4: R30.1, U13.4, U16.4, U17.2, U18.2
NET_U14_1: R2.1, U14.1, U14.2
PROC_CAN1_RX: U1.A9, U4.4
PROC_CAN1_TX: U1.B9, U4.1
PROC_CAN2_RX: U1.M2, U6.4
PROC_CAN2_TX: U1.A8, U6.1
PROC_FMC_A0: U1.F11, U8.E2
PROC_FMC_A1: U1.E9, U8.D2
PROC_FMC_A2: U1.F10, U8.C2
PROC_FMC_A3: U1.G11, U8.A2
PROC_FMC_A4: U1.F9, U8.B2
PROC_FMC_A5: U1.F8, U8.D3
PROC_FMC_A6: U1.N7, U8.C3
PROC_FMC_A7: U1.K6, U8.A3
PROC_FMC_A8: U1.L6, U8.B6
PROC_FMC_A9: U1.M6, U8.A6
PROC_FMC_A10: U1.N6, U8.C6
PROC_FMC_A11: U1.K5, U8.D6
PROC_FMC_A12: U1.J1, U8.B7
PROC_FMC_A13: U1.G3, U8.A7
PROC_FMC_A14: U1.G5, U8.C7
PROC_FMC_A15: U1.G6, U8.D7
PROC_FMC_A16: U1.K2, U8.E7
PROC_FMC_A17: U1.H6, U8.B3
PROC_FMC_A18: U1.H5, U8.C4
PROC_FMC_A19: U1.C10, U8.D5
PROC_FMC_A20: U1.B11, U8.D4
PROC_FMC_A21: U1.D9, U8.C5
PROC_FMC_A22: U1.E8, U8.B8
PROC_FMC_A23: U1.D8, U8.C8
PROC_FMC_D0: U1.J2, U8.E3
PROC_FMC_D1: U1.K1, U8.H3
PROC_FMC_D2: U1.B3, U8.E4
PROC_FMC_D3: U1.C4, U8.H4
PROC_FMC_D4: U1.L5, U8.H5
PROC_FMC_D5: U1.M5, U8.E5
PROC_FMC_D6: U1.N5, U8.H6
PROC_FMC_D7: U1.J4, U8.E6
PROC_FMC_D8: U1.K4, U8.F3
PROC_FMC_D9: U1.L4, U8.G3
PROC_FMC_D10: U1.N4, U8.F4
PROC_FMC_D11: U1.M4, U8.G4
PROC_FMC_D12: U1.L3, U8.F5
PROC_FMC_D13: U1.L2, U8.G6
PROC_FMC_D14: U1.M1, U8.F6
PROC_FMC_D15: U1.H4, U8.G7
PROC_FMC_NBL0: R23.1, U1.B10, U8.F7
PROC_FMC_NE2: R19.1, U1.E5, U8.F2
PROC_FMC_NOE: R20.1, U1.B5, U8.G2
PROC_FMC_NWAIT: U1.F4, U8.A4
PROC_FMC_NWE: R21.1, U1.A4, U8.A5
PROC_SPI1_MISO: U1.C7, U2.2
PROC_SPI1_MOSI: U1.C8, U2.5
PROC_SPI1_NSS: R14.1, U1.C2, U2.1
PROC_SPI1_SCK: U1.M9, U2.6
PROC_SYS_JTCK_SWCLK: U1.B1, U3.9
PROC_SYS_JTDO_SWO: U1.B7, U3.13
PROC_SYS_JTMS_SWDIO: U1.D3, U3.7
RST_OUT_U3_SRESET_B: R16.1, U3.15, U16.1
VCC_S1_8V5: C32.1, C34.1, C37.1, C38.1, J1.1, R24.2, U11.4, U12.8
VCC_TIER1_3V3: C1.1, C2.1, C3.1, C4.1, C5.1, C6.1, C7.1, C8.1, C9.1, C10.1, C11.1, C12.1, C13.1, C14.1, C15.1, C16.1, C23.1, C24.1, C25.1, C27.1, C28.1, C29.1, C30.1, C33.1, C36.1, C39.1, C40.1, C41.1, F1.2, R7.2, R8.2, R9.2, R10.2, R13.2, R14.2, R15.2, R16.2, R19.2, R20.2, R21.2, R22.2, R23.2, R25.1, R30.2, R31.2, R33.1, U1.A1, U1.C1, U1.C5, U1.C11, U1.D7, U1.E6, U1.E10, U1.G1, U1.G7, U1.J5, U1.J6, U1.J7, U1.J8, U1.L1, U2.8, U3.1, U4.3, U6.5, U8.D8, U8.F1, U8.G5, U10.4, U11.5, U13.6, U16.5, U17.5, U18.5
VCC_TIER1_5V0: C26.1, C35.1, R27.2, R28.1, U6.3, U12.1
